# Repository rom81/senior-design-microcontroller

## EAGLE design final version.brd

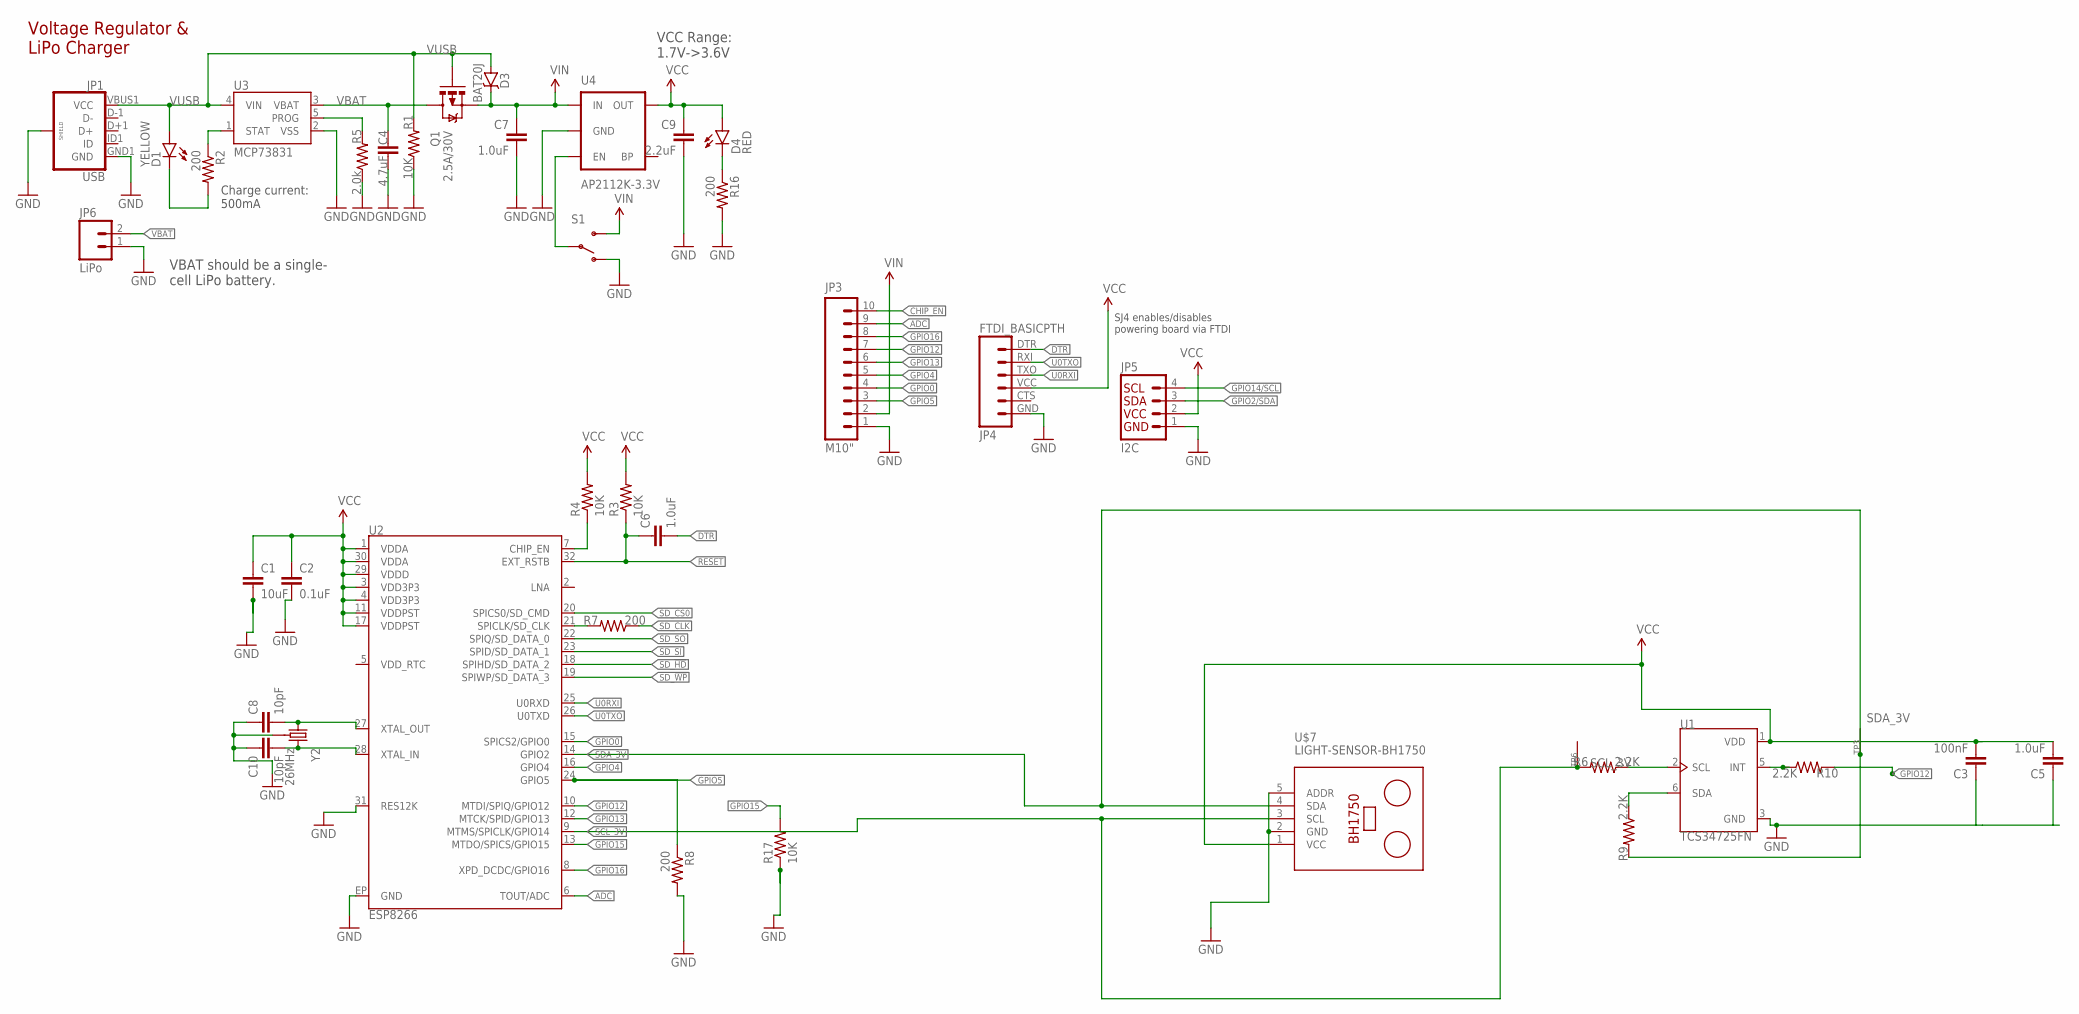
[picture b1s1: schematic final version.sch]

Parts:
C1: 10uF; 0603-CAP
C2: 0.1uF; 0603-CAP
C3: 100nF; 0603-CAP
C4: 4.7uF; 0603-CAP
C5, C6: 1.0uF; 0603-CAP
C7: 1.0uF; 0805
C8, C10: 10pF; 0603-CAP
C9: 2.2uF; 0603-CAP
D1: YELLOW; LED-0603
D3: BAT20J; SOD-323
D4: RED; LED-0603
JP1: USB; USB-B-MICRO-SMD_V03
JP3: M10"; 1X10
JP4: FTDI_BASICPTH; FTDI_BASIC
JP5: I2C; 1X04
JP6: LiPo; JST-2-PTH
Q1: 2.5A/30V; SOT23-3
R1, R3, R4, R17: 10K; 0603-RES
R2, R7, R8, R16: 200; 0603-RES
R5: 2.0k; 0603-RES
R6, R9, R10: 2.2K; 0603-RES
S1: SWITCH-SPDT-SMD-A; SWITCH-SPST-SMD-A
TP3, TP6: SEWTAP0.5IN; SEWINGTAP_0.5
U1: TCS34725FN; SON65P200X240X70-6N
U2: ESP8266; QFN32
U3: MCP73831; SOT23-5
U4: AP2112K-3.3V; SOT23-5
U$7: LIGHT-SENSOR-BH1750
Y2: 26MHz; CRYSTAL-SMD-3.2X2.5

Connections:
ADC: JP3.9, U2.6 (TOUT/ADC)
CHIP_EN: JP3.10, R4.1, U2.7 (CHIP_EN)
DTR: C6.2, JP4.DTR (1)
GND: C1.2, C2.2, C3.1, C4.2, C5.1, C7.2, C8.1, C9.2, C10.1, JP1.GND1 (GND), JP1.SHIELD1 (SHIELD), JP1.SHIELD2 (SHIELD), JP1.SHIELD3 (SHIELD), JP3.1, JP4.GND (6), JP5.1, JP6.1, R1.1, R5.1, R8.2, R16.2, R17.1, S1.1 (O), U1.3 (GND), U2.31 (RES12K), U2.EP (GND), U3.2 (VSS), U4.2 (GND), U$7.2 (GND), U$7.5 (ADDR), Y2.2 (GND), Y2.4 (GND)
GPIO0: JP3.4, U2.15 (SPICS2/GPIO0)
GPIO2/SDA: JP5.3
GPIO4: JP3.5, U2.16 (GPIO4)
GPIO5: JP3.3, R8.1, U2.24 (GPIO5)
GPIO12: JP3.7, U2.10 (MTDI/SPIQ/GPIO12)
GPIO13: JP3.6, U2.12 (MTCK/SPID/GPIO13)
GPIO14/SCL: JP5.4
GPIO15: R17.2, U2.13 (MTDO/SPICS/GPIO15)
GPIO16: JP3.8, U2.8 (XPD_DCDC/GPIO16)
unnamed: R10.1, U1.5 (INT)
unnamed: R9.1, U1.6 (SDA)
unnamed: R6.1, U1.2 (SCL)
unnamed: C10.2, U2.28 (XTAL_IN), Y2.3 (2)
unnamed: D4.C, R16.1
unnamed: C8.2, U2.27 (XTAL_OUT), Y2.1
unnamed: S1.2, U4.3 (EN)
unnamed: R7.2, U2.21 (SPICLK/SD_CLK)
unnamed: R5.2, U3.5 (PROG)
unnamed: D1.C, R2.2
unnamed: R2.1, U3.1 (STAT)
RESET: C6.1, R3.1, U2.32 (EXT_RSTB)
SCL_3V: R6.2, TP6.TAP, U2.9 (MTMS/SPICLK/GPIO14), U$7.3 (SCL)
SDA_3V: R9.2, TP3.TAP, U2.14 (GPIO2), U$7.4 (SDA)
SD_!HD!: U2.18 (SPIHD/SD_DATA_2)
SD_!WP!: U2.19 (SPIWP/SD_DATA_3)
SD_CLK: R7.1
SD_CS0: U2.20 (SPICS0/SD_CMD)
SD_SI: U2.23 (SPID/SD_DATA_1)
SD_SO: U2.22 (SPIQ/SD_DATA_0)
U0RXI: JP4.TXO (3), U2.25 (U0RXD)
U0TXO: JP4.RXI (2), U2.26 (U0TXD)
VBAT: C4.1, JP6.2, Q1.3 (D), U3.3 (VBAT)
VCC: C1.1, C2.1, C3.2, C5.2, C9.1, D4.A, JP4.VCC (4), JP5.2, R3.2, R4.2, U1.1 (VDD), U2.1 (VDDA), U2.3 (VDD3P3), U2.4 (VDD3P3), U2.11 (VDDPST), U2.17 (VDDPST), U2.29 (VDDD), U2.30 (VDDA), U4.5 (OUT), U$7.1 (VCC)
VIN: C7.1, D3.C, JP3.2, Q1.2 (S), S1.3 (S), U4.1 (IN)
VUSB: D1.A, D3.A, JP1.VBUS1 (VCC), Q1.1 (G), R1.2, U3.4 (VIN)

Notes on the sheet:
SJ4 enables/disables powering board via FTDI
Voltage Regulator & LiPo Charger
VCC Range: 1.7V->3.6V
VBAT should be a single- cell LiPo battery.
Charge current: 500mA

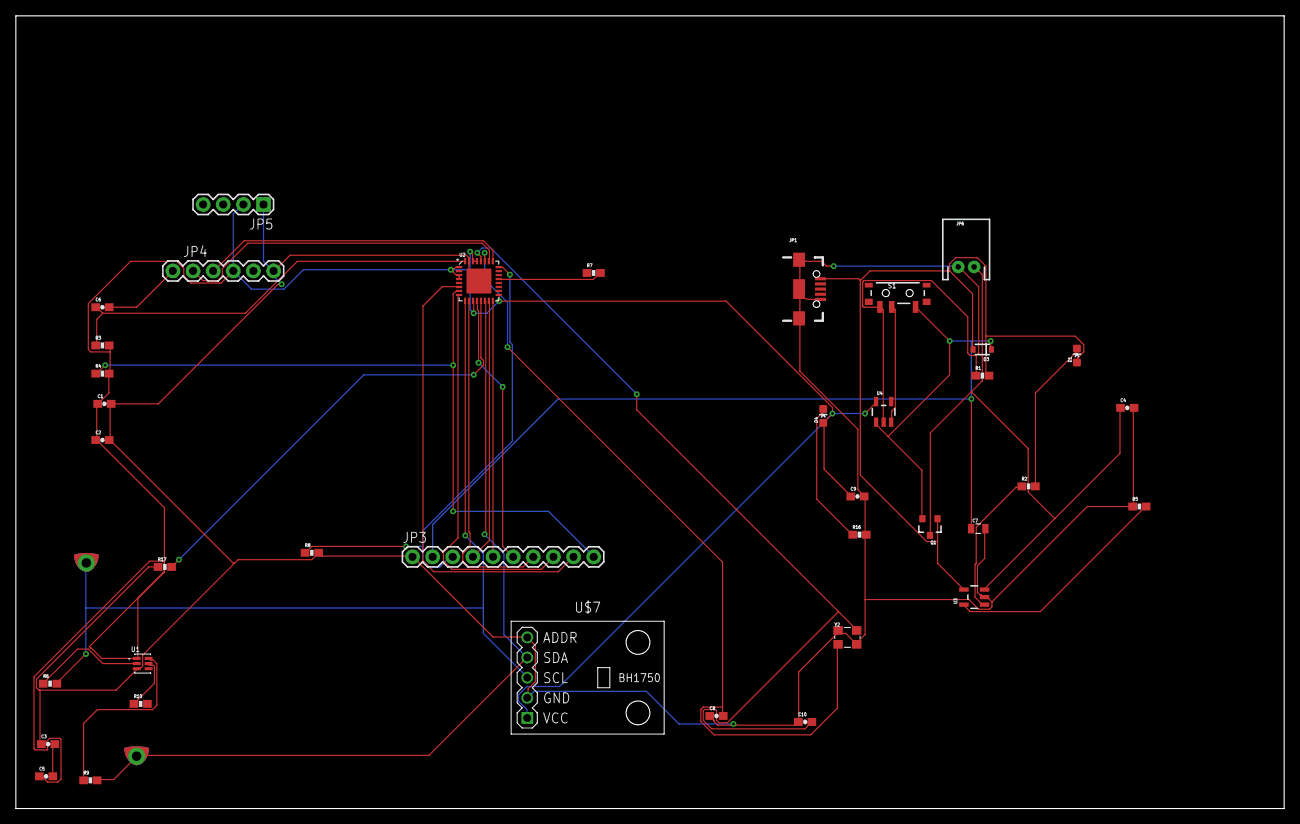
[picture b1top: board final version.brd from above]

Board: 2 copper layers, 160.0 x 100.0 mm, 40 parts (0 on the bottom side), 31 nets.

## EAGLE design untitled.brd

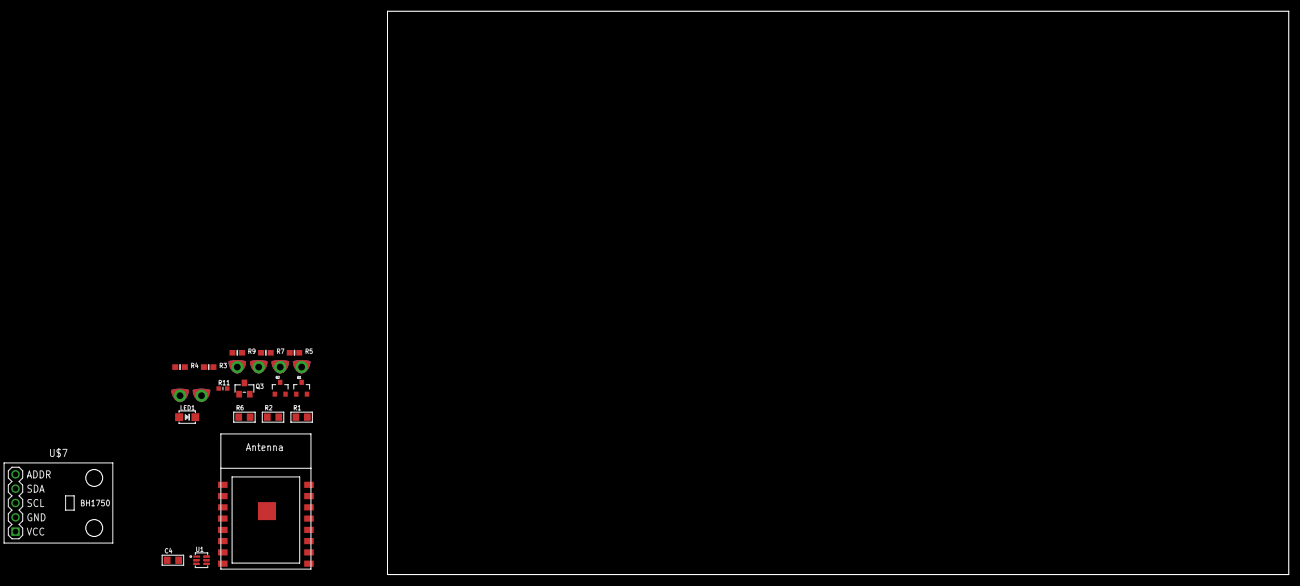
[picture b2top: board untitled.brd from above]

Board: 2 copper layers, 160.0 x 100.0 mm, 23 parts (0 on the bottom side), 17 nets, no tracks yet.

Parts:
C4: 0.1µF; _0805
LED1: 45-21/LK2C-B38452C4CB2/2T; EVERLIGHT_45-21
Q1, Q2: mmbt2222; SOT23-3
Q3: BSS138; SOT23-WIDE
R1, R2, R6: 10K; _0805
R3, R5, R7, R9: 10K; 0603-NO
R4: 4.7K; 0603-NO
R11: 1K; _0603MP
TP1, TP2, TP3, TP4, TP5, TP6: SEWTAP0.5IN; SEWINGTAP_0.5
U1: TCS34725; TCS3472_FN6
U$7: LIGHT-SENSOR-BH1750
X2: ESP-12; ESP-12S

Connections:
3.3V: R3.2, R9.2, X2.2, X2.8
+3V3: C4.1, LED1.A, R1.2, R2.2, R6.2, TP1.TAP, U1.P$1, U$7.1
CH_PD: R3.1, X2.3
DTR: Q2.2, R5.1
GND: C4.2, Q3.2, R4.1, TP2.TAP, U1.P$3, U$7.2, X2.9, X2.P$1
GPIO0: Q2.3, X2.12
GPIO2: R9.1, X2.11
GPIO15: R4.2, X2.10
INT: Q3.1, R6.1, U1.P$5
unnamed: LED1.K, Q3.3
unnamed: Q1.1, R5.2
unnamed: Q2.1, R7.2
RESET: Q1.3, X2.1
RTS: Q1.2, R7.1
RXD: R11.2, X2.15
SCL_3V: R1.1, TP5.TAP, TP6.TAP, U1.P$2
SDA_3V: R2.1, TP3.TAP, TP4.TAP, U1.P$6

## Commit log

2019-02-13 Initial messing around with ESP8266 -- working on connecting to wifi, creating infrastructure for connecting to MQTT broker, and interfacing with BH1750
2019-03-05 Added infrastructure for connecting to MQTT client. Currently successfully connects to mqtt client
2019-03-06 added support for topics
2019-03-22 1. Added I2C bus addresses of each sensor 2. Built out JSON stuff 3. Interfaced with TCS over I2C interface (currently only reading the hardcoded serial number on the device)
2019-03-23 Create Eagle

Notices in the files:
parts and their libraries:
SparkFun-Capacitors: Licensing: Creative Commons ShareAlike 4.0 International - https://creativecommons.org/licenses/by-sa/4.0
diy-modules: Released under the Creative Commons Attribution 4.0 International License: http://creativecommons.org/licenses/by/4.0
